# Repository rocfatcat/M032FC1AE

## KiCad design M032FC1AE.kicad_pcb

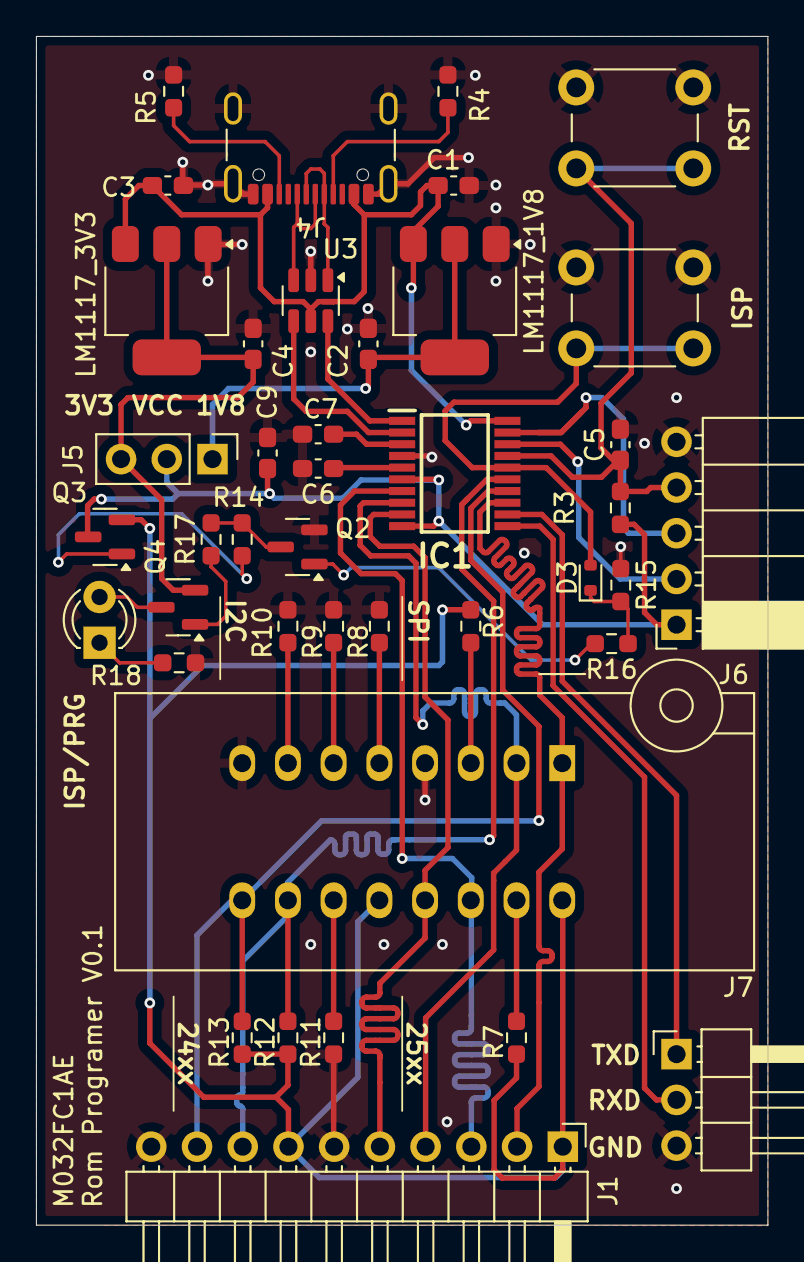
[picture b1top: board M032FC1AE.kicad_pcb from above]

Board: 2 copper layers, 40.6 x 66.0 mm, 41 parts (0 on the bottom side), 39 nets.

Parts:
C1, C2, C3, C4: 10uf; C_0603_1608Metric_Pad1.08x0.95mm_HandSolder
C5, C6, C7, C9: 1uf; C_0603_1608Metric_Pad1.08x0.95mm_HandSolder
D3: 1N4148WT; D_SOD-523
IC1: M032FC1AE
ISP: SW_Push; SW_PUSH_6mm
ISP/PRG: LED; LED_D3.0mm
J1: Conn_01x10; PinHeader_1x10_P2.54mm_Horizontal
J2: Conn_01x03; PinHeader_1x03_P2.54mm_Horizontal
J4: USB_C_Receptacle_USB2.0_16P; USB_C_Receptacle_GCT_USB4105-xx-A_16P_TopMnt_Horizontal
J5: Conn_01x03; PinHeader_1x03_P2.54mm_Vertical
J6: Conn_01x05; PinSocket_1x05_P2.54mm_Horizontal
J7: Conn_02x08_Counter_Clockwise; DIP_Socket-16_W4.3_W5.08_W7.62_W10.16_W10.9_3M_216-3340-00-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
LM1117_1V8: AMS1117-1.8; SOT-223-3_TabPin2
LM1117_3V3: AMS1117-3.3; SOT-223-3_TabPin2
Q2: SS8050; SOT-23
Q3: FDN340P; SOT-23
Q4: SS8550; SOT-23
R3, R14, R16, R17: 10k; R_0603_1608Metric_Pad0.98x0.95mm_HandSolder
R4, R5: 5.1k; R_0603_1608Metric_Pad0.98x0.95mm_HandSolder
R6, R7, R8, R9, R10, R11, R12, R13: 330; R_0603_1608Metric_Pad0.98x0.95mm_HandSolder
R15: 100k; R_0603_1608Metric_Pad0.98x0.95mm_HandSolder
R18: 150R; R_0603_1608Metric_Pad0.98x0.95mm_HandSolder
RST: SW_Push; SW_PUSH_6mm
U3: USBLC6-2SC6; SOT-23-6

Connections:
+3.3V: C4.1, J5.3, LM1117_3V3.2 (VO), Q4.2 (E)
GND: C1.2, C2.2, C3.2, C4.2, C5.2, C6.2, C7.2, C9.2, IC1.4 (VSS), ISP.1, J1.6, J1.10, J2.3, J4.A1 (GND), J4.A12 (GND), J4.B1 (GND), J4.B12 (GND), J4.S1 (SHIELD), J6.5, J7.4, J7.8, LM1117_1V8.1 (GND), LM1117_3V3.1 (GND), Q2.2 (E), R4.2, R5.2, R8.1, R9.1, R10.1, R11.2, R15.1, R18.2, RST.1, U3.2 (GND)
ISP: D3.2 (A), IC1.16 (PA.0), ISP.2
unnamed: ISP/PRG.2 (A), Q4.3 (C)
unnamed: ISP/PRG.1 (K), R18.1
unnamed: D3.1 (K), R15.2, R16.1
unnamed: C6.1, IC1.5 (LDO_CAP)
unnamed: C7.1, IC1.3 (USB_VDD33_CAP)
unnamed: J4.A5 (CC1), R4.1
unnamed: J4.B5 (CC2), R5.1
unnamed: J4.A6 (D+), J4.B6 (D+), U3.3 (I/O2)
unnamed: J4.A7 (D-), J4.B7 (D-), U3.1 (I/O1)
unnamed: C2.1, J5.1, LM1117_1V8.2 (VO)
unnamed: J7.3, R6.2
unnamed: J7.5, R8.2
unnamed: J7.6, R9.2
unnamed: J7.7, R10.2
unnamed: J7.11, R11.1
unnamed: J7.15, R7.1
unnamed: Q2.1 (B), R16.2
unnamed: Q3.1 (G), R14.2
unnamed: Q4.1 (B), R17.1
PWR_CTL: Q2.3 (C), R14.1, R17.2
USB_D+: IC1.2 (USB_D+), U3.4 (I/O2)
USB_D-: IC1.1 (USB_D-), U3.6 (I/O1)
VBUS: C1.1, C3.1, IC1.20 (USB_VBUS), J4.A4 (VBUS), J4.A9 (VBUS), J4.B4 (VBUS), J4.B9 (VBUS), LM1117_1V8.3 (VI), LM1117_3V3.3 (VI), U3.5 (VBUS)
VCC: C9.1, IC1.6 (VDD), IC1.10 (AVDD), J5.2, J6.1, Q3.3 (D), R3.1
VCC_IO: J1.1, J1.7, J7.12, J7.16, Q3.2 (S), R6.1, R7.2, R12.1, R13.1
bus_spi_clk: IC1.7 (PB.14), J1.3, J7.14
bus_spi_miso: IC1.8 (PB.13), J1.4, J7.2
bus_spi_mosi: IC1.9 (PB.12), J1.5, J7.13
bus_spi_ss: IC1.13 (PA.3), J1.2, J7.1
bus_usci1_clk: IC1.15 (PA.1), J1.8, J7.10, R12.2
bus_usci1_data: IC1.14 (PA.2), J1.9, J7.9, R13.2
ice_clk: IC1.19 (PF.1), J6.3
ice_dat: IC1.18 (PF.0), J6.2
rst: C5.1, IC1.17 (NRESET), J6.4, R3.2, RST.2
uart_rx: IC1.12 (PF.2), J2.1
uart_tx: IC1.11 (PF.3), J2.2

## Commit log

2025-08-06 Init
2025-09-05 ffffff
2025-09-08 fffff
2025-09-08 ddddd
2025-09-09 ffffddd
2025-09-16 dfdfdfdf
2025-09-19 lalala
2025-10-02 Update Modify
2025-10-02 Release Gerver V0.1
